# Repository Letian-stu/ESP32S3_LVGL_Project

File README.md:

# ESP32S3_LVGL_Project

## https://www.bilibili.com/video/BV1f8411b7uX/?spm_id_from=333.999.0.0&vd_source=5a3738895b167685395154934912a846

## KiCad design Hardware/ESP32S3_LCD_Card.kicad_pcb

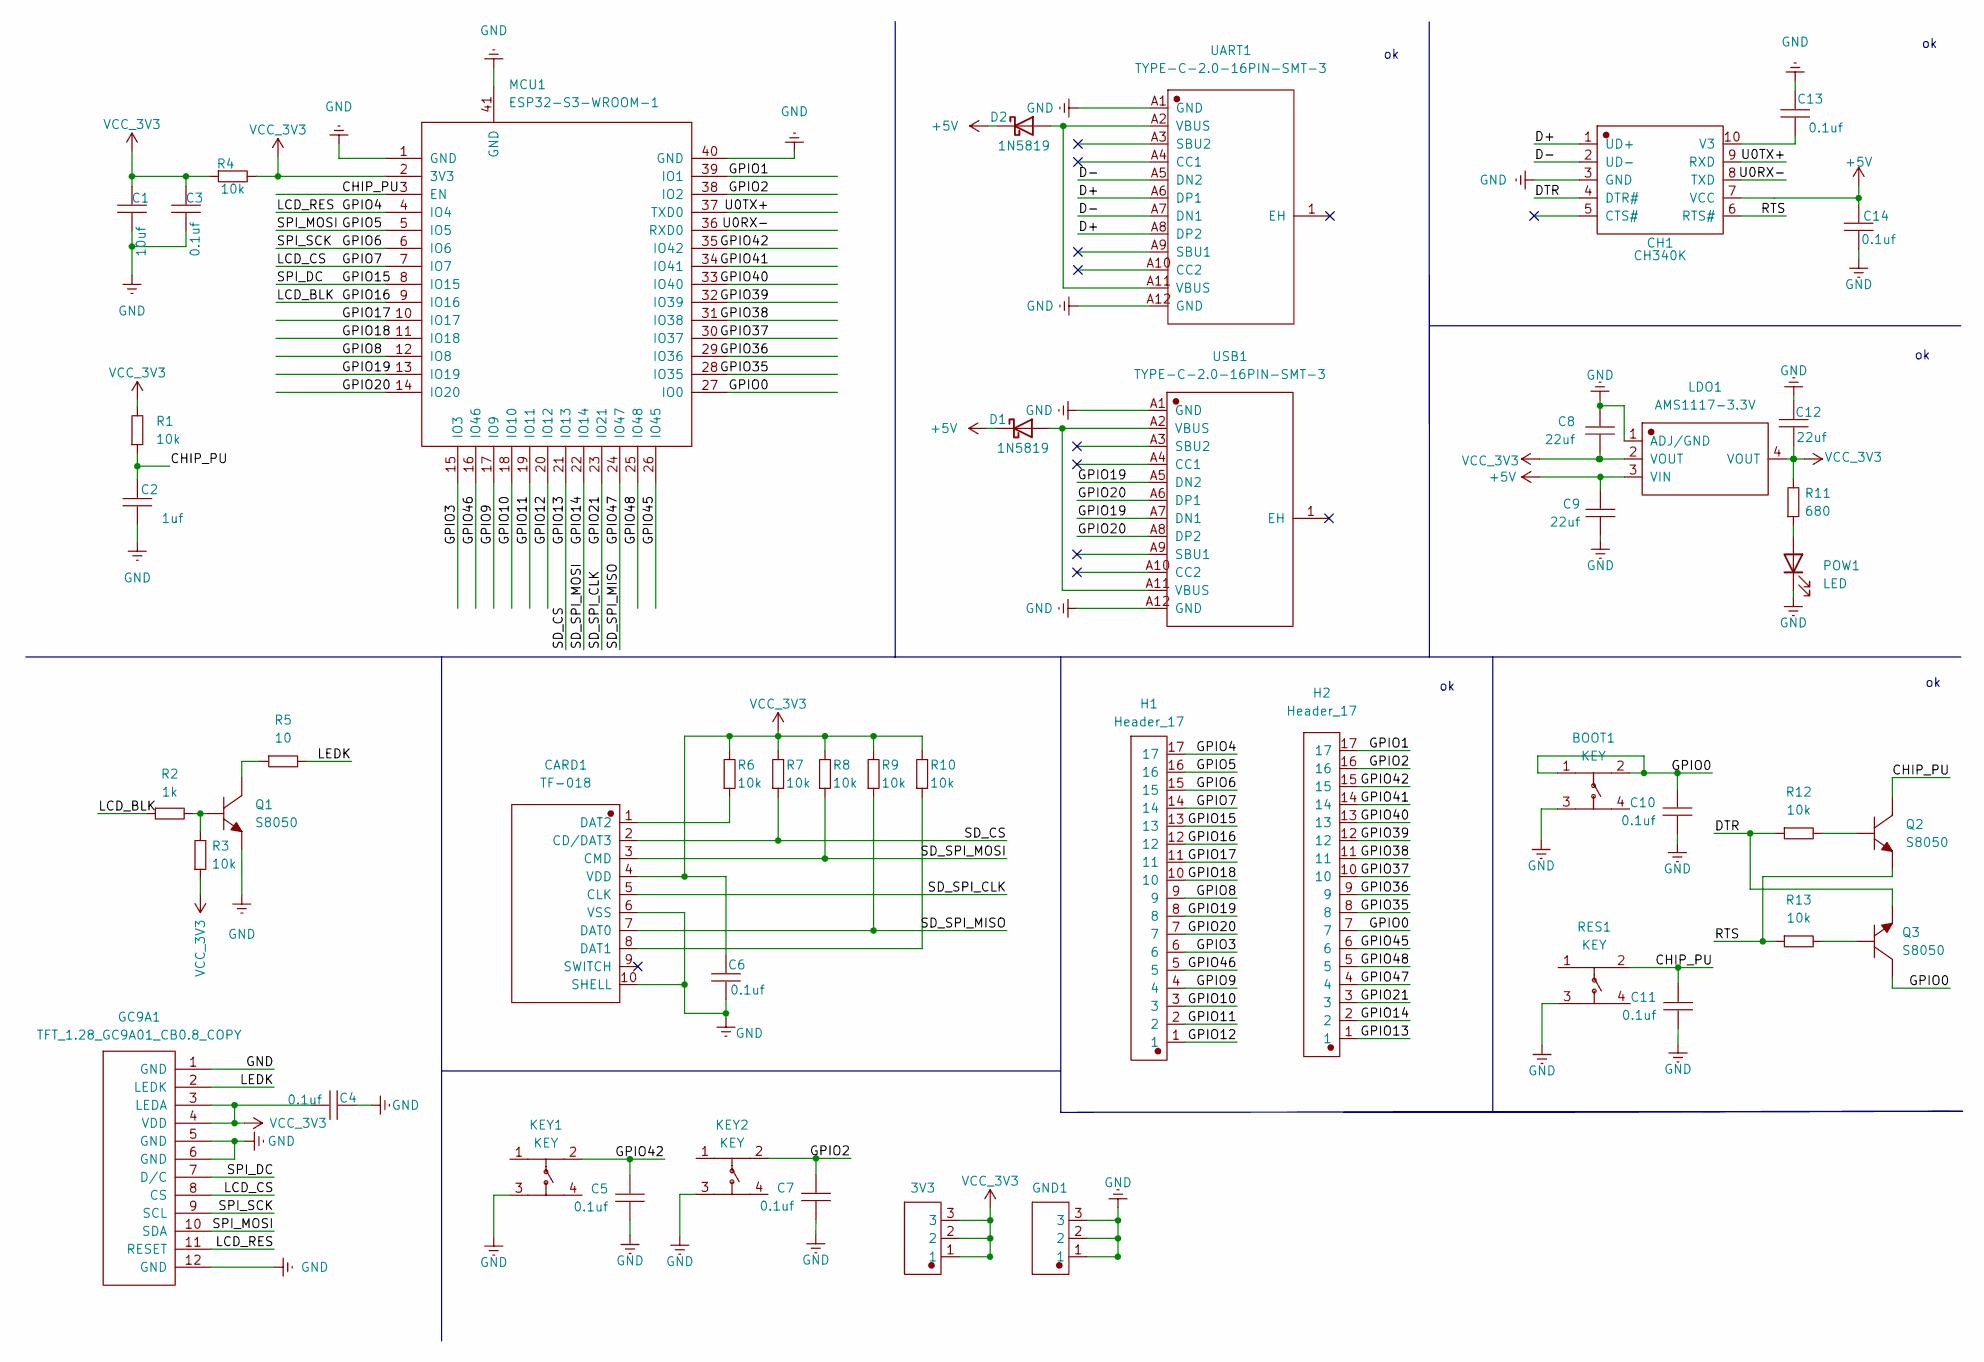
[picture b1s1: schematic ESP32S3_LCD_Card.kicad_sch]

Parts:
3V3: Header_3; HDR-F-2.54_1X3
BOOT1: KEY; KEY-SMD_4P-L4.2-W3.2-P2.20-LS4.6
C1: 10uf; C0603
C2: 1uf; C0603
C3, C4, C5, C6, C7, C10, C11, C13, C14: 0.1uf; C0603
C8, C9, C12: 22uf; C0603
CARD1: TF-018; TF-SMD_TF-018
CH1: CH340K; ESOP-10_L4.9-W3.9-P1.00-LS6.2-BL-EP
D1, D2: 1N5819; 0805_R
GC9A1: TFT_1.28_GC9A01_CB0.8_COPY; TFT_1.28_GC9A01_CB0.8
GND1: Header_3; HDR-F-2.54_1X3
H1, H2: Header_17; HEADER17
KEY1, KEY2: KEY; KEY-SMD_4P-L4.2-W3.2-P2.20-LS4.6
LDO1: AMS1117-3.3V; SOT-223-4_L6.5-W3.5-P2.30-LS7.0-BR
MCU1: ESP32-S3-WROOM-1
POW1: LED; L0603
Q1, Q2, Q3: S8050; SOT-23-3_L2.9-W1.3-P1.90-LS2.4-BR
R1, R3, R4, R6, R7, R8, R9, R10, R12, R13: 10k; R0603
R2: 1k; R0603
R5: 10; R0603
R11: 680; R0603
RES1: KEY; KEY-SMD_4P-L4.2-W3.2-P2.20-LS4.6
UART1: TYPE-C-2.0-16PIN-SMT-3; TYPE-C-SMD_TYPE-CF3.1
USB1: TYPE-C-2.0-16PIN-SMT-3; TYPE-C-SMD_TYPE-CF3.1

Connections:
+5V: C9.1, C14.1, CH1.7 (VCC), D1.1 (K), D2.1 (K), LDO1.3 (VIN)
/CHIP_PU: C2.2, C11.1, MCU1.3 (EN), Q2.3 (C), R1.1, RES1.2
/D+: CH1.1 (UD+), UART1.A6 (DP1), UART1.A8 (DP2)
/D-: CH1.2 (UD-), UART1.A5 (DN2), UART1.A7 (DN1)
/DTR: CH1.4 (DTR#), Q3.2 (E), R12.1
/GPIO0: BOOT1.1, BOOT1.2, C10.1, H2.7, MCU1.27 (IO0), Q3.3 (C)
/GPIO1: H2.17, MCU1.39 (IO1)
/GPIO2: C7.1, H2.16, KEY2.2, MCU1.38 (IO2)
/GPIO3: H1.6, MCU1.15 (IO3)
/GPIO4: GC9A1.11 (RESET), H1.17, MCU1.4 (IO4)
/GPIO5: GC9A1.10 (SDA), H1.16, MCU1.5 (IO5)
/GPIO6: GC9A1.9 (SCL), H1.15, MCU1.6 (IO6)
/GPIO7: GC9A1.8 (CS), H1.14, MCU1.7 (IO7)
/GPIO8: H1.9, MCU1.12 (IO8)
/GPIO9: H1.4, MCU1.17 (IO9)
/GPIO10: H1.3, MCU1.18 (IO10)
/GPIO11: H1.2, MCU1.19 (IO11)
/GPIO12: H1.1, MCU1.20 (IO12)
/GPIO13: CARD1.2 (CD/DAT3), H2.1, MCU1.21 (IO13), R7.1
/GPIO14: CARD1.3 (CMD), H2.2, MCU1.22 (IO14), R8.1
/GPIO15: GC9A1.7 (D/C), H1.13, MCU1.8 (IO15)
/GPIO16: H1.12, MCU1.9 (IO16), R2.1
/GPIO17: H1.11, MCU1.10 (IO17)
/GPIO18: H1.10, MCU1.11 (IO18)
/GPIO19: H1.8, MCU1.13 (IO19), USB1.A5 (DN2), USB1.A7 (DN1)
/GPIO20: H1.7, MCU1.14 (IO20), USB1.A6 (DP1), USB1.A8 (DP2)
/GPIO21: CARD1.5 (CLK), H2.3, MCU1.23 (IO21)
/GPIO35: H2.8, MCU1.28 (IO35)
/GPIO36: H2.9, MCU1.29 (IO36)
/GPIO37: H2.10, MCU1.30 (IO37)
/GPIO38: H2.11, MCU1.31 (IO38)
/GPIO39: H2.12, MCU1.32 (IO39)
/GPIO40: H2.13, MCU1.33 (IO40)
/GPIO41: H2.14, MCU1.34 (IO41)
/GPIO42: C5.1, H2.15, KEY1.2, MCU1.35 (IO42)
/GPIO45: H2.6, MCU1.26 (IO45)
/GPIO46: H1.5, MCU1.16 (IO46)
/GPIO47: CARD1.7 (DAT0), H2.4, MCU1.24 (IO47), R9.1
/GPIO48: H2.5, MCU1.25 (IO48)
/LEDK: GC9A1.2 (LEDK), R5.2
/RTS: CH1.6 (RTS#), Q2.2 (E), R13.1
/U0RX-: CH1.8 (TXD), MCU1.36 (RXD0)
/U0TX+: CH1.9 (RXD), MCU1.37 (TXD0)
GND: BOOT1.3, C1.1, C2.1, C3.1, C4.2, C5.2, C6.1, C7.2, C8.2, C9.2, C10.2, C11.2, C12.2, C13.2, C14.2, CARD1.6 (VSS), CARD1.10 (SHELL), CH1.3 (GND), GC9A1.1 (GND), GC9A1.5 (GND), GC9A1.6 (GND), GC9A1.12 (GND), GND1.1, GND1.2, GND1.3, KEY1.3, KEY2.3, LDO1.1 (ADJ/GND), MCU1.1 (GND), MCU1.40 (GND), MCU1.41 (GND), POW1.1 (K), Q1.2 (E), RES1.3, UART1.A1 (GND), UART1.A12 (GND), USB1.A1 (GND), USB1.A12 (GND)
unnamed: C13.1, CH1.10 (V3)
unnamed: CARD1.1 (DAT2), R6.1
unnamed: CARD1.8 (DAT1), R10.1
unnamed: D1.2 (A), USB1.A2 (VBUS), USB1.A11 (VBUS)
unnamed: D2.2 (A), UART1.A2 (VBUS), UART1.A11 (VBUS)
unnamed: POW1.2 (A), R11.1
unnamed: Q1.1 (B), R2.2, R3.2
unnamed: Q1.3 (C), R5.1
unnamed: Q2.1 (B), R12.2
unnamed: Q3.1 (B), R13.2
VCC: 3V3.1, 3V3.2, 3V3.3, C1.2, C3.2, C4.1, C6.2, C8.1, C12.1, CARD1.4 (VDD), GC9A1.3 (LEDA), GC9A1.4 (VDD), LDO1.2 (VOUT), LDO1.4 (VOUT), MCU1.2 (3V3), R1.2, R3.1, R4.1, R4.2, R6.2, R7.2, R8.2, R9.2, R10.2, R11.2

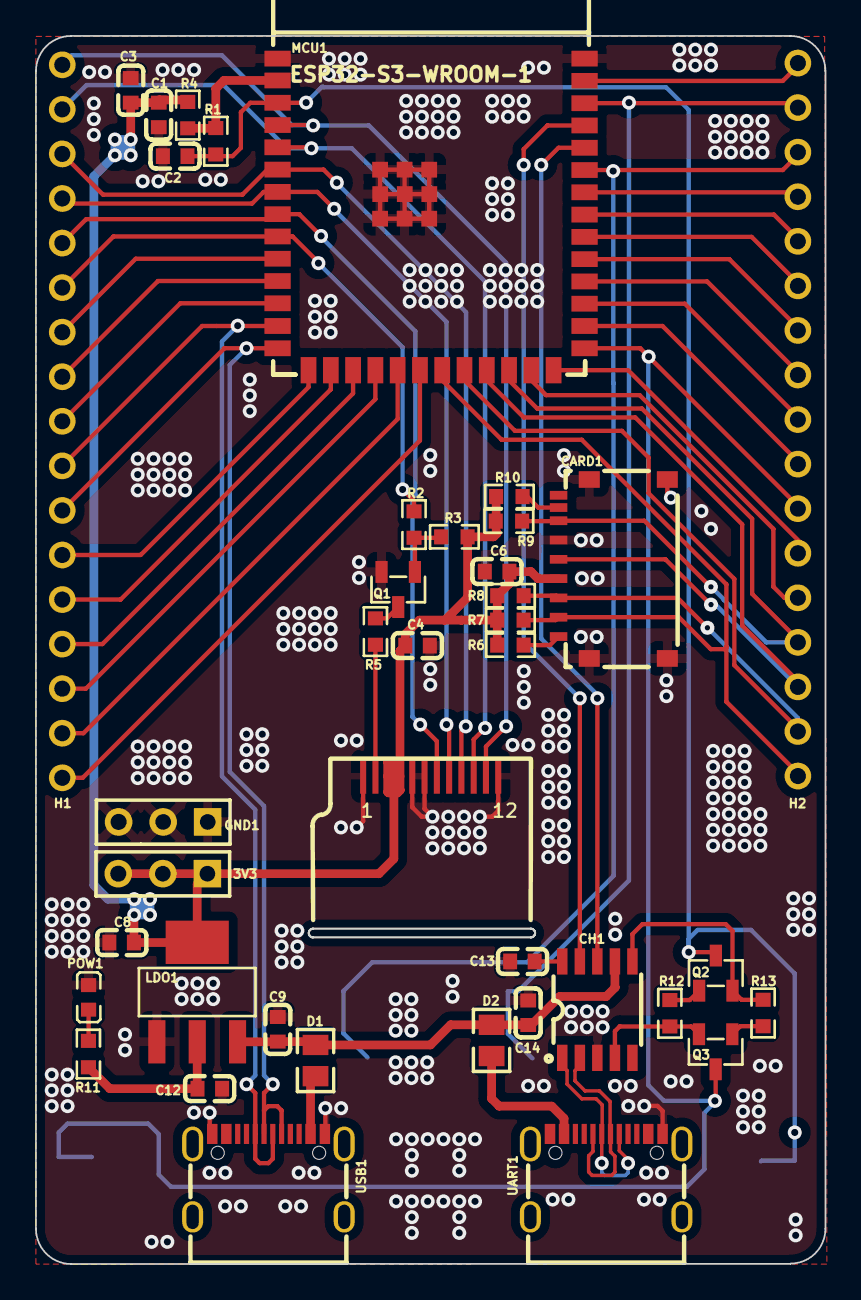
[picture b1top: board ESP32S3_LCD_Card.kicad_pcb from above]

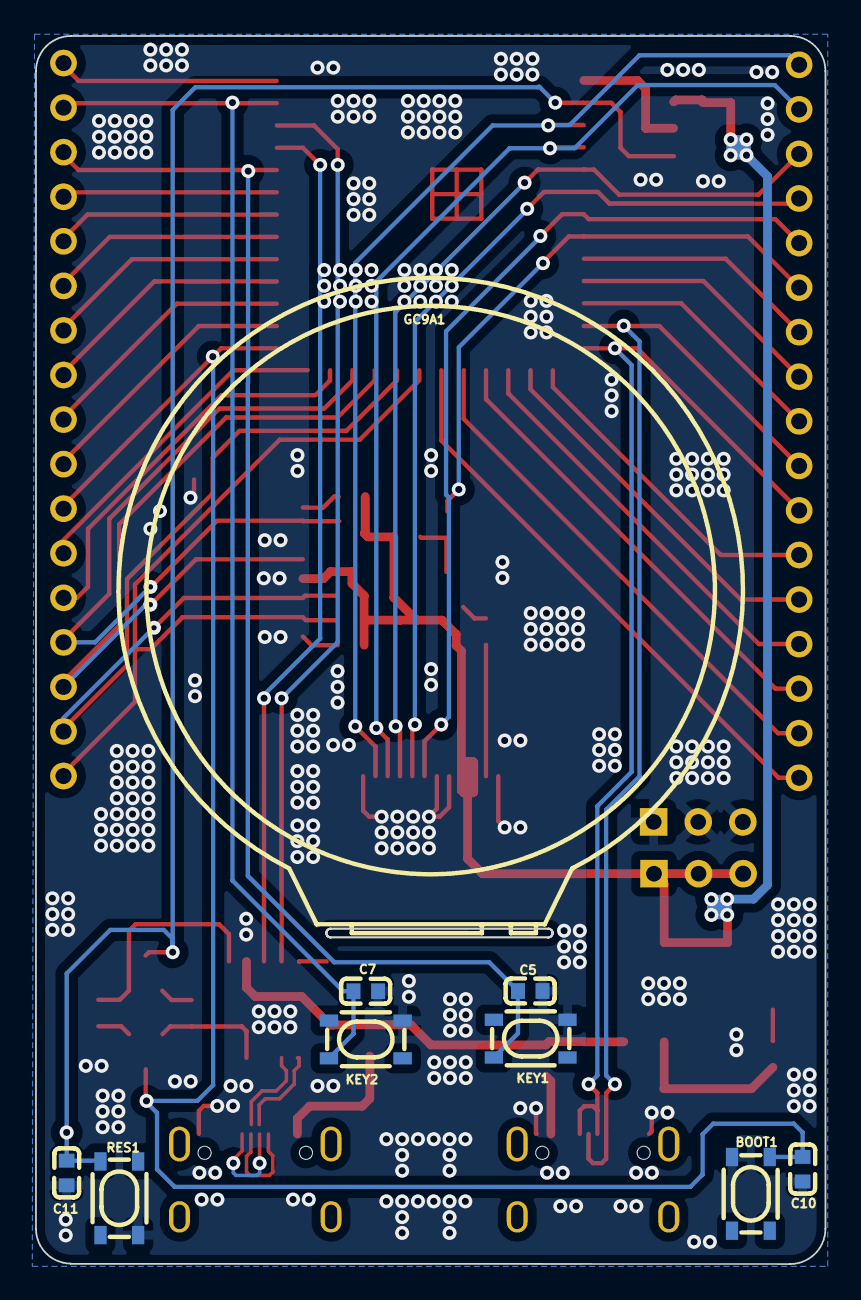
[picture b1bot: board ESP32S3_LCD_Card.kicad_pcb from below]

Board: 2 copper layers, 45.0 x 70.0 mm, 48 parts (9 on the bottom side), 55 nets.

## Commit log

2022-09-09 my first commit
2022-09-11 change ui
2022-09-13 0913
2022-09-13 add Hardware
2022-09-13 first master
2022-09-16 integrat project
2022-09-16 09/16
2022-09-23 09/23
2022-11-10 11/10
2022-11-10 11.10
2022-11-10 11.10.5.2
